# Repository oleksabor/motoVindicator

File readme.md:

## motorcycle Voltage Indicator

The stator coils have burned on my bike recently. 
It has no voltage indicator installed so I've started to look for a problem only when the battery was depleted twice.

The idea is to have green light between 12.5V and 15V and a warning lights otherwise.

Can be used on any other vechle that requires small control light for the battery.

### Schema
I've used the [Допълнение 1 schema](http://www.kn34pc.com/construct/kolo_hristov_av_rgb.html) as the most simple one (do not care about the current)

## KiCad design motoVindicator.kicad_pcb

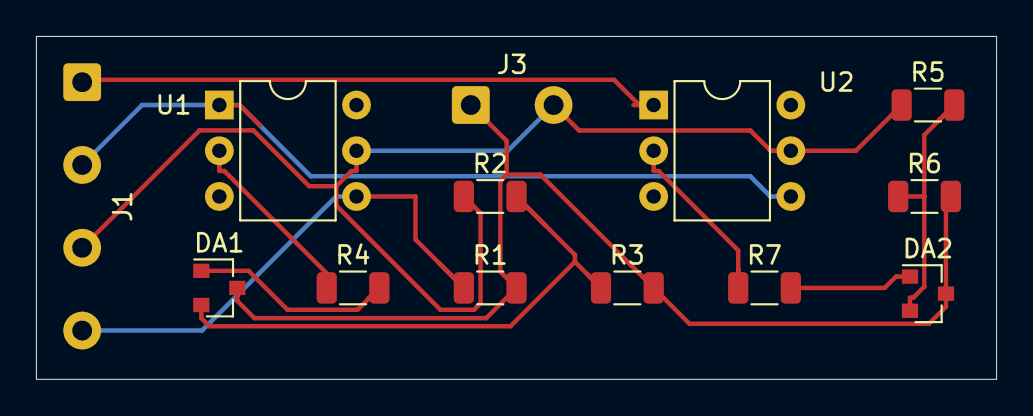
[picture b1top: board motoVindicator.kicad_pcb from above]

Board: 2 copper layers, 53.3 x 19.0 mm, 13 parts (0 on the bottom side), 11 nets.

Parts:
DA1, DA2: TL431DBZ; SOT-23
J1: Conn_01x04_Male; SolderWire-0.5sqmm_1x04_P4.6mm_D0.9mm_OD2.1mm
J3: Conn_01x02_Male; SolderWire-0.5sqmm_1x02_P4.6mm_D0.9mm_OD2.1mm
R1, R4, R7: 2.2k; R_1206_3216Metric
R2, R5: 100k; R_1206_3216Metric
R3: 26k; R_1206_3216Metric
R6: 20k; R_1206_3216Metric
U1, U2: 4N37; DIP-6_W7.62mm

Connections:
unnamed: DA1.1, R4.2
unnamed: DA1.2, R2.2, R3.1
unnamed: DA1.3, DA2.3, J3.1, R1.2, R3.2, R6.2
unnamed: DA2.1, R7.2
unnamed: DA2.2, R5.2, R6.1
unnamed: J1.1, U2.1
unnamed: J1.2, U1.1, U2.4
unnamed: J1.3, J3.2, R2.1, R5.1, U1.5, U2.5
unnamed: J1.4, R1.1, U1.4
unnamed: R4.1, U1.2
unnamed: R7.1, U2.2

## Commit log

2021-06-28 initial with connectors
2021-06-28 missed sch and pcb picture
2021-06-28 ignoring net ses and dsn files
2021-06-29 schemas were added
2021-06-29 fixing image references
2021-06-29 space in image name was replaced
2021-06-29 description adjusted
2021-07-01 R3 and R6 adjusted
2021-07-19 exported
